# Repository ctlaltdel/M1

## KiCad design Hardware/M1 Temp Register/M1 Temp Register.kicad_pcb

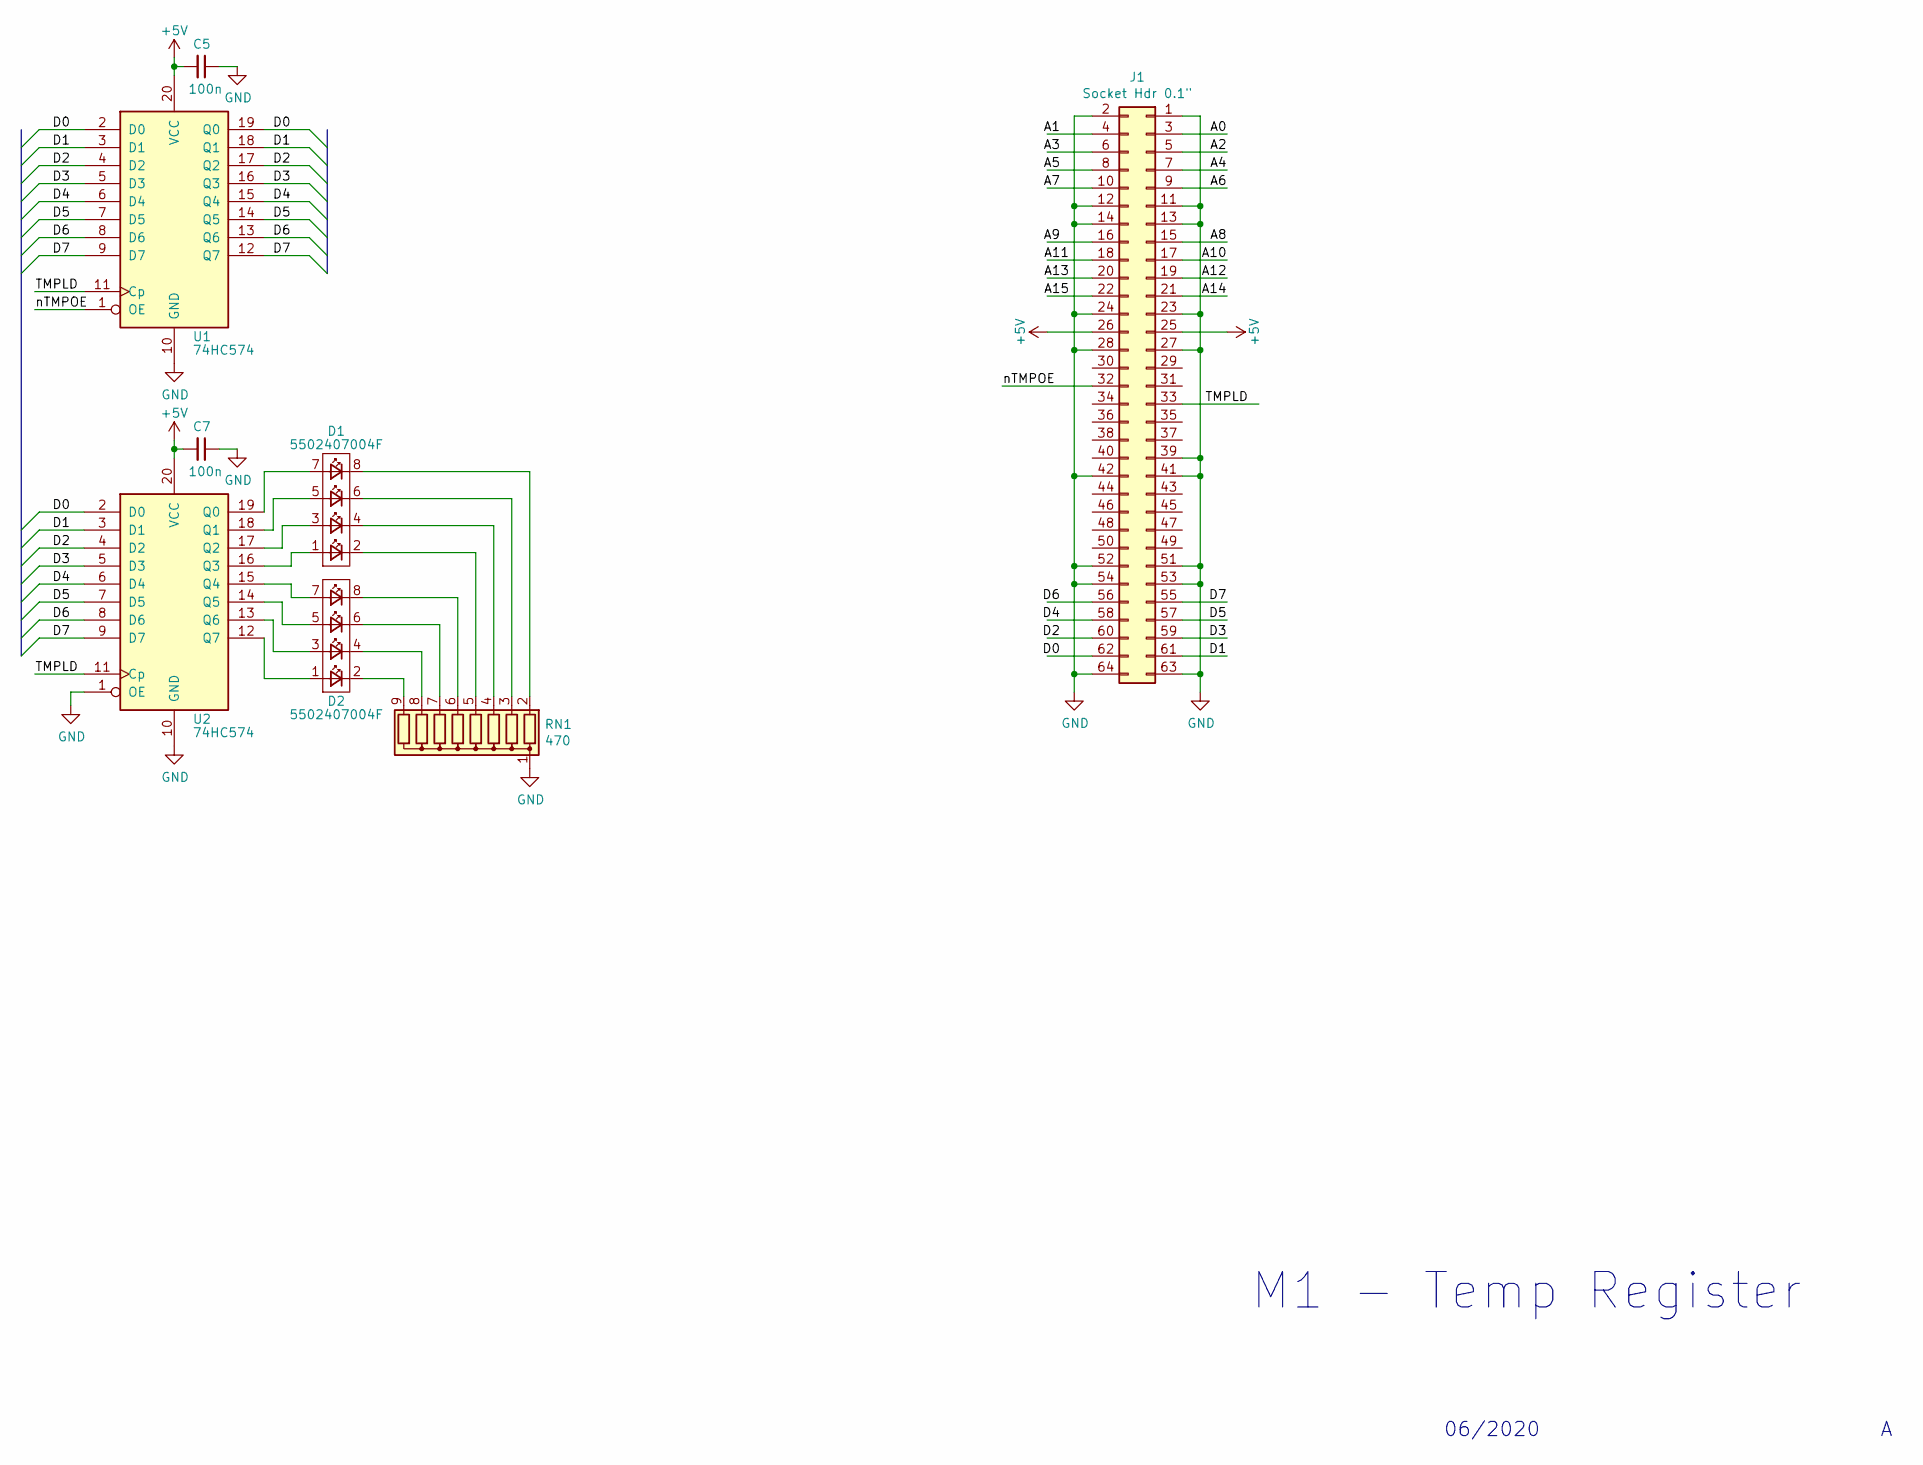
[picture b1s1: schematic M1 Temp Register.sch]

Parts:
C5, C7: 100n; C_Disc_D5.1mm_W3.2mm_P5.00mm
D1, D2: 5502407004F
J1: Socket Hdr 0.1\"; IDC-Header_2x32_P2.54mm_Horizontal
RN1: 470; R_Array_SIP9
U1, U2: 74HC574; DIP-20_W7.62mm_Socket

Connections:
+5V: C5.2, C7.2, J1.25, J1.26, U1.20 (VCC), U2.20 (VCC)
/A0: J1.3
/A1: J1.4
/A2: J1.5
/A3: J1.6
/A4: J1.7
/A5: J1.8
/A6: J1.9
/A7: J1.10
/A8: J1.15
/A9: J1.16
/A10: J1.17
/A11: J1.18
/A12: J1.19
/A13: J1.20
/A14: J1.21
/A15: J1.22
/D0: J1.62, U1.2 (D0), U1.19 (Q0), U2.2 (D0)
/D1: J1.61, U1.3 (D1), U1.18 (Q1), U2.3 (D1)
/D2: J1.60, U1.4 (D2), U1.17 (Q2), U2.4 (D2)
/D3: J1.59, U1.5 (D3), U1.16 (Q3), U2.5 (D3)
/D4: J1.58, U1.6 (D4), U1.15 (Q4), U2.6 (D4)
/D5: J1.57, U1.7 (D5), U1.14 (Q5), U2.7 (D5)
/D6: J1.56, U1.8 (D6), U1.13 (Q6), U2.8 (D6)
/D7: J1.55, U1.9 (D7), U1.12 (Q7), U2.9 (D7)
/TMPLD: J1.33, U1.11 (Cp), U2.11 (Cp)
/nTMPOE: J1.32, U1.1 (OE)
GND: C5.1, C7.1, J1.1, J1.2, J1.11, J1.12, J1.13, J1.14, J1.23, J1.24, J1.27, J1.28, J1.39, J1.41, J1.42, J1.51, J1.52, J1.53, J1.54, J1.63, J1.64, RN1.1 (common), U1.10 (GND), U2.1 (OE), U2.10 (GND)
unnamed: D1.1, U2.16 (Q3)
unnamed: D1.2, RN1.5 (R4)
unnamed: D1.3, U2.17 (Q2)
unnamed: D1.4, RN1.4 (R3)
unnamed: D1.5, U2.18 (Q1)
unnamed: D1.6, RN1.3 (R2)
unnamed: D1.7, U2.19 (Q0)
unnamed: D1.8, RN1.2 (R1)
unnamed: D2.1, U2.12 (Q7)
unnamed: D2.2, RN1.9 (R8)
unnamed: D2.3, U2.13 (Q6)
unnamed: D2.4, RN1.8 (R7)
unnamed: D2.5, U2.14 (Q5)
unnamed: D2.6, RN1.7 (R6)
unnamed: D2.7, U2.15 (Q4)
unnamed: D2.8, RN1.6 (R5)

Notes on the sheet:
M1 - Temp Register
06/2020

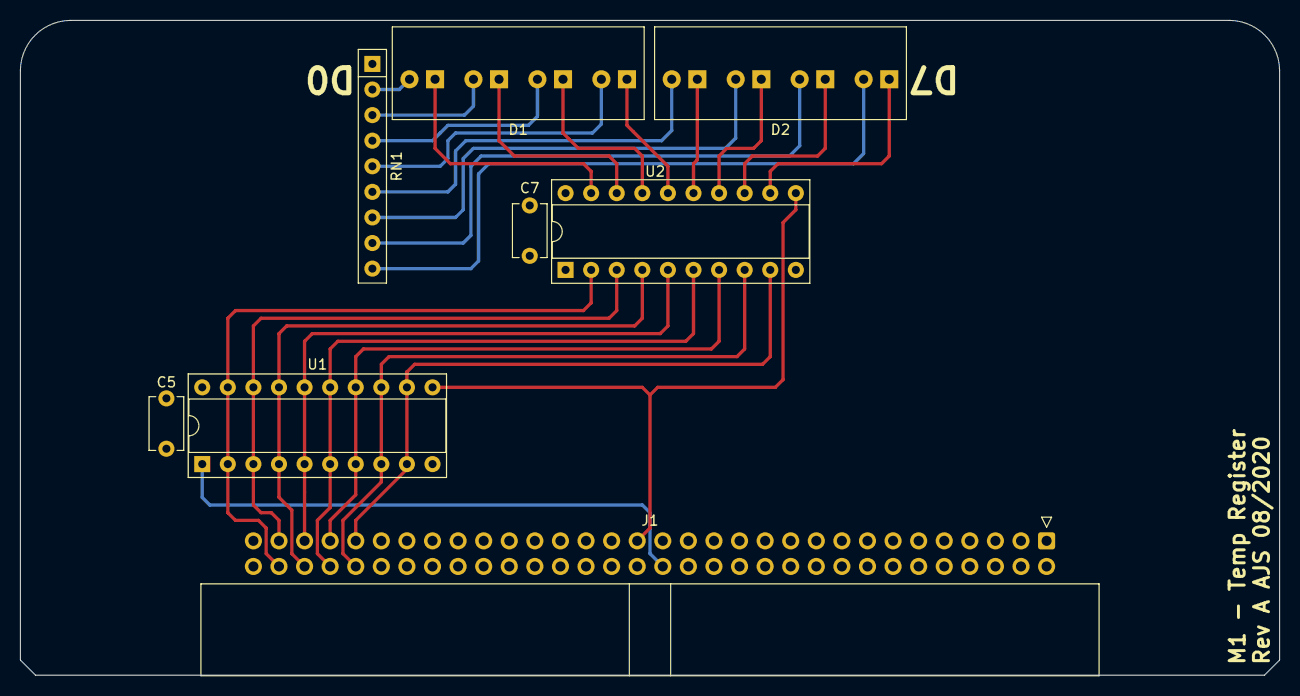
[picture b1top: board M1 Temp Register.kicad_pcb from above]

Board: 4 copper layers, 125.0 x 65.0 mm, 8 parts (0 on the bottom side), 28 nets.

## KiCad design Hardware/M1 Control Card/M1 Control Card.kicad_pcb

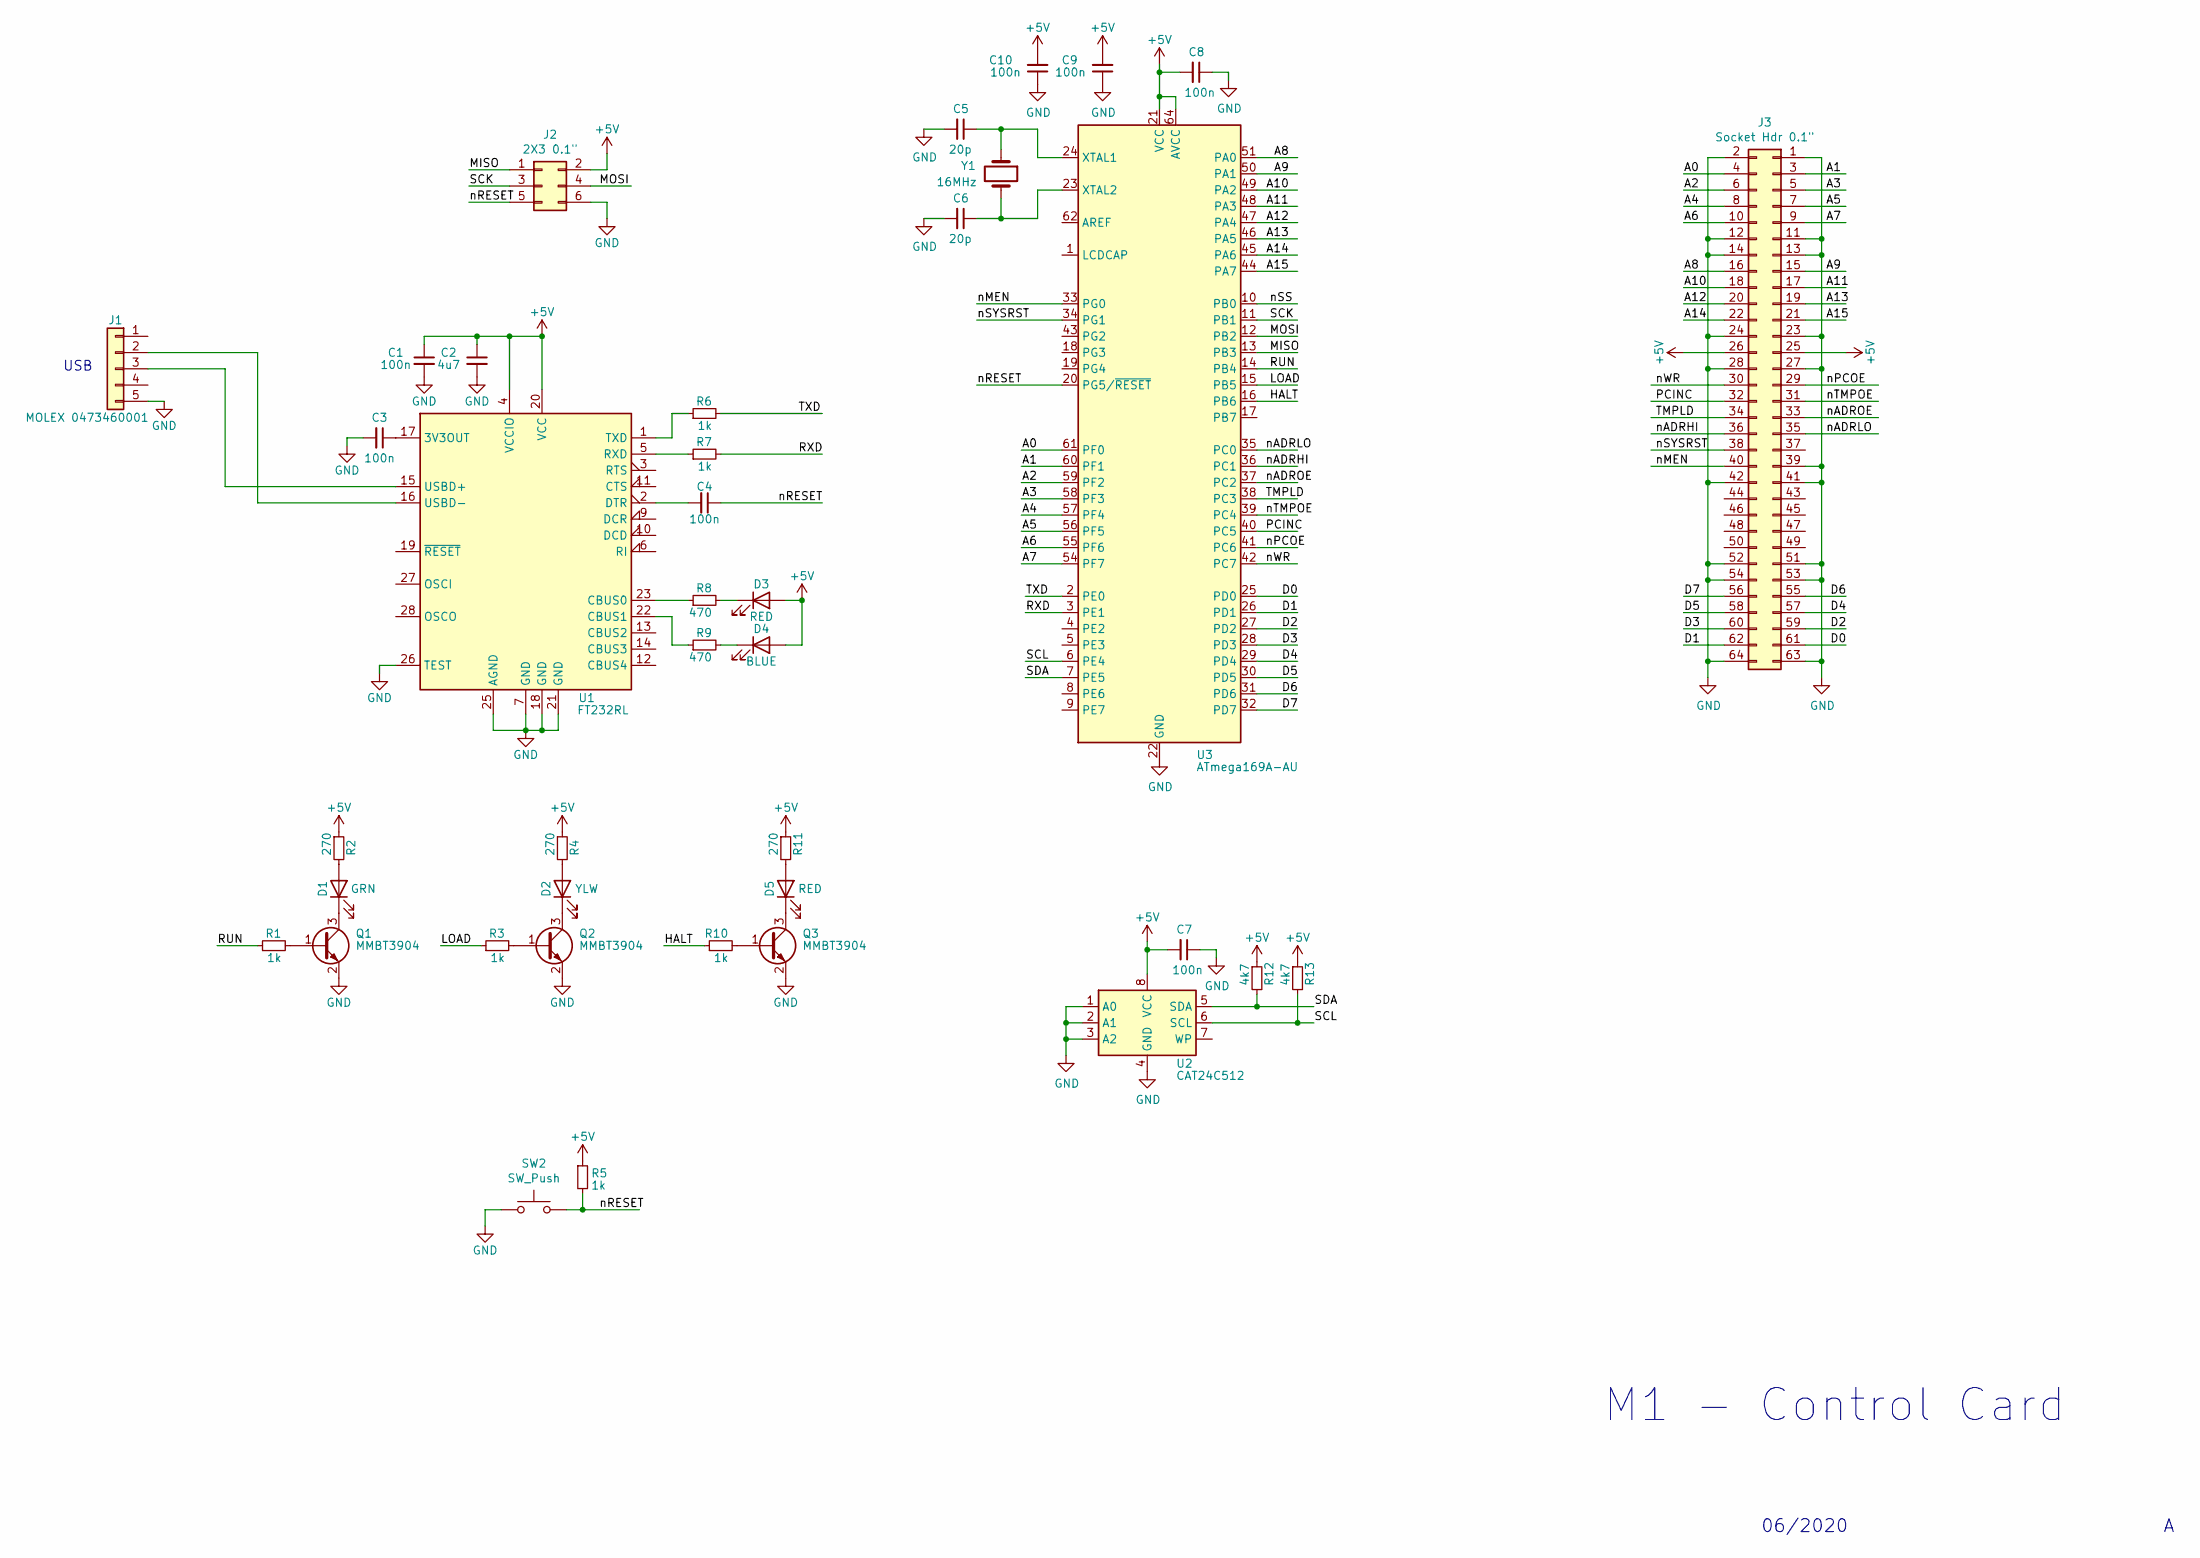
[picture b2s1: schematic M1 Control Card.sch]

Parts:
C1, C3, C4, C7, C8, C9, C10: 100n; C_0402_1005Metric
C2: 4u7; C_0603_1608Metric
C5, C6: 20p; C_0402_1005Metric
D1: GRN; LED_0603_1608Metric
D2: YLW; LED_0603_1608Metric
D3, D5: RED; LED_0603_1608Metric
D4: BLUE; LED_0603_1608Metric
J1: MOLEX 0473460001; USB_Micro-B_Molex_47346-0001
J2: 2X3 0.1\"; PinHeader_2x03_P2.54mm_Horizontal
J3: Socket Hdr 0.1\"; IDC-Header_2x32_P2.54mm_Horizontal
Q1, Q2, Q3: MMBT3904; SOT-23
R1, R3, R5, R6, R7, R10: 1k; R_0402_1005Metric
R2, R4, R11: 270; R_0402_1005Metric
R8, R9: 470; R_0402_1005Metric
R12, R13: 4k7; R_0402_1005Metric
SW2: SW_Push; SW_SPST_PTS645
U1: FT232RL; SSOP-28_5.3x10.2mm_P0.65mm
U2: CAT24C512; SOIC-8_3.9x4.9mm_P1.27mm
U3: ATmega169A-AU; TQFP-64_14x14mm_P0.8mm
Y1: 16MHz; Crystal_SMD_Abracon_ABM3-2Pin_5.0x3.2mm

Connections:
+5V: C1.1, C2.1, C7.2, C8.2, C9.2, C10.2, D3.2 (A), D4.2 (A), J2.2, J3.25, J3.26, R2.1, R4.1, R5.1, R11.1, R12.1, R13.1, U1.4 (VCCIO), U1.20 (VCC), U2.8 (VCC), U3.21 (VCC), U3.52 (VCC), U3.64 (AVCC)
/A0: J3.4, U3.61 (PF0)
/A1: J3.3, U3.60 (PF1)
/A2: J3.6, U3.59 (PF2)
/A3: J3.5, U3.58 (PF3)
/A4: J3.8, U3.57 (PF4)
/A5: J3.7, U3.56 (PF5)
/A6: J3.10, U3.55 (PF6)
/A7: J3.9, U3.54 (PF7)
/A8: J3.16, U3.51 (PA0)
/A9: J3.15, U3.50 (PA1)
/A10: J3.18, U3.49 (PA2)
/A11: J3.17, U3.48 (PA3)
/A12: J3.20, U3.47 (PA4)
/A13: J3.19, U3.46 (PA5)
/A14: J3.22, U3.45 (PA6)
/A15: J3.21, U3.44 (PA7)
/ADRHI: J3.36, U3.36 (PC1)
/D0: J3.61, U3.25 (PD0)
/D1: J3.62, U3.26 (PD1)
/D2: J3.59, U3.27 (PD2)
/D3: J3.60, U3.28 (PD3)
/D4: J3.57, U3.29 (PD4)
/D5: J3.58, U3.30 (PD5)
/D6: J3.55, U3.31 (PD6)
/D7: J3.56, U3.32 (PD7)
/HALT: R10.1, U3.16 (PB6)
/LOAD: R3.1, U3.15 (PB5)
/MISO: J2.1, U3.13 (PB3)
/MOSI: J2.4, U3.12 (PB2)
/PCINC: J3.32, U3.40 (PC5)
/RUN: R1.1, U3.14 (PB4)
/RXD: R7.2, U3.3 (PE1)
/SCK: J2.3, U3.11 (PB1)
/SCL: R13.2, U2.6 (SCL), U3.6 (PE4)
/SDA: R12.2, U2.5 (SDA), U3.7 (PE5)
/TMPLD: J3.34, U3.38 (PC3)
/TXD: R6.2, U3.2 (PE0)
/nADRLO: J3.35, U3.35 (PC0)
/nADROE: J3.33, U3.37 (PC2)
/nMEN: J3.40, U3.33 (PG0)
/nPCOE: J3.29, U3.41 (PC6)
/nRESET: C4.1, J2.5, R5.2, SW2.2, U3.20 (PG5/~RESET)
/nSS: U3.10 (PB0)
/nSYSRST: J3.38, U3.34 (PG1)
/nTMPOE: J3.31, U3.39 (PC4)
/nWR: J3.30, U3.42 (PC7)
GND: C1.2, C2.2, C3.2, C5.2, C6.2, C7.1, C8.1, C9.1, C10.1, J1.5, J2.6, J3.1, J3.2, J3.11, J3.12, J3.13, J3.14, J3.23, J3.24, J3.27, J3.28, J3.39, J3.41, J3.42, J3.51, J3.52, J3.53, J3.54, J3.63, J3.64, Q1.2 (E), Q2.2 (E), Q3.2 (E), SW2.1, U1.7 (GND), U1.18 (GND), U1.21 (GND), U1.25 (AGND), U1.26 (TEST), U2.1 (A0), U2.2 (A1), U2.3 (A2), U2.4 (GND), U3.22 (GND), U3.53 (GND), U3.63 (GND)
unnamed: C3.1, U1.17 (3V3OUT)
unnamed: C4.2, U1.2 (DTR)
unnamed: C5.1, U3.24 (XTAL1), Y1.1
unnamed: C6.1, U3.23 (XTAL2), Y1.2
unnamed: D1.1 (K), Q1.3 (C)
unnamed: D1.2 (A), R2.2
unnamed: D2.1 (K), Q2.3 (C)
unnamed: D2.2 (A), R4.2
unnamed: D3.1 (K), R8.2
unnamed: D4.1 (K), R9.2
unnamed: D5.1 (K), Q3.3 (C)
unnamed: D5.2 (A), R11.2
unnamed: J1.2, U1.16 (USBD-)
unnamed: J1.3, U1.15 (USBD+)
unnamed: Q1.1 (B), R1.2
unnamed: Q2.1 (B), R3.2
unnamed: Q3.1 (B), R10.2
unnamed: R6.1, U1.1 (TXD)
unnamed: R7.1, U1.5 (RXD)
unnamed: R8.1, U1.23 (CBUS0)
unnamed: R9.1, U1.22 (CBUS1)

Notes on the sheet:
USB
M1 - Control Card
06/2020

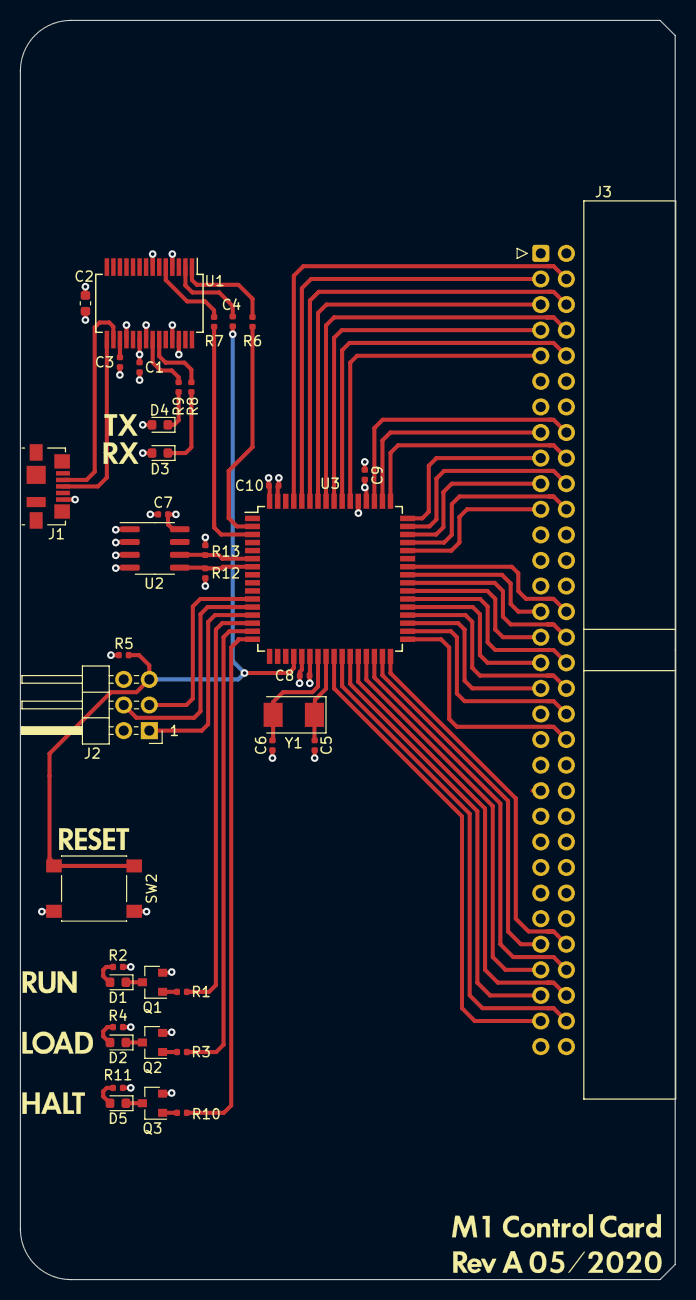
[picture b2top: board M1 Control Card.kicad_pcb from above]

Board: 4 copper layers, 65.0 x 125.0 mm, 39 parts (0 on the bottom side), 68 nets.

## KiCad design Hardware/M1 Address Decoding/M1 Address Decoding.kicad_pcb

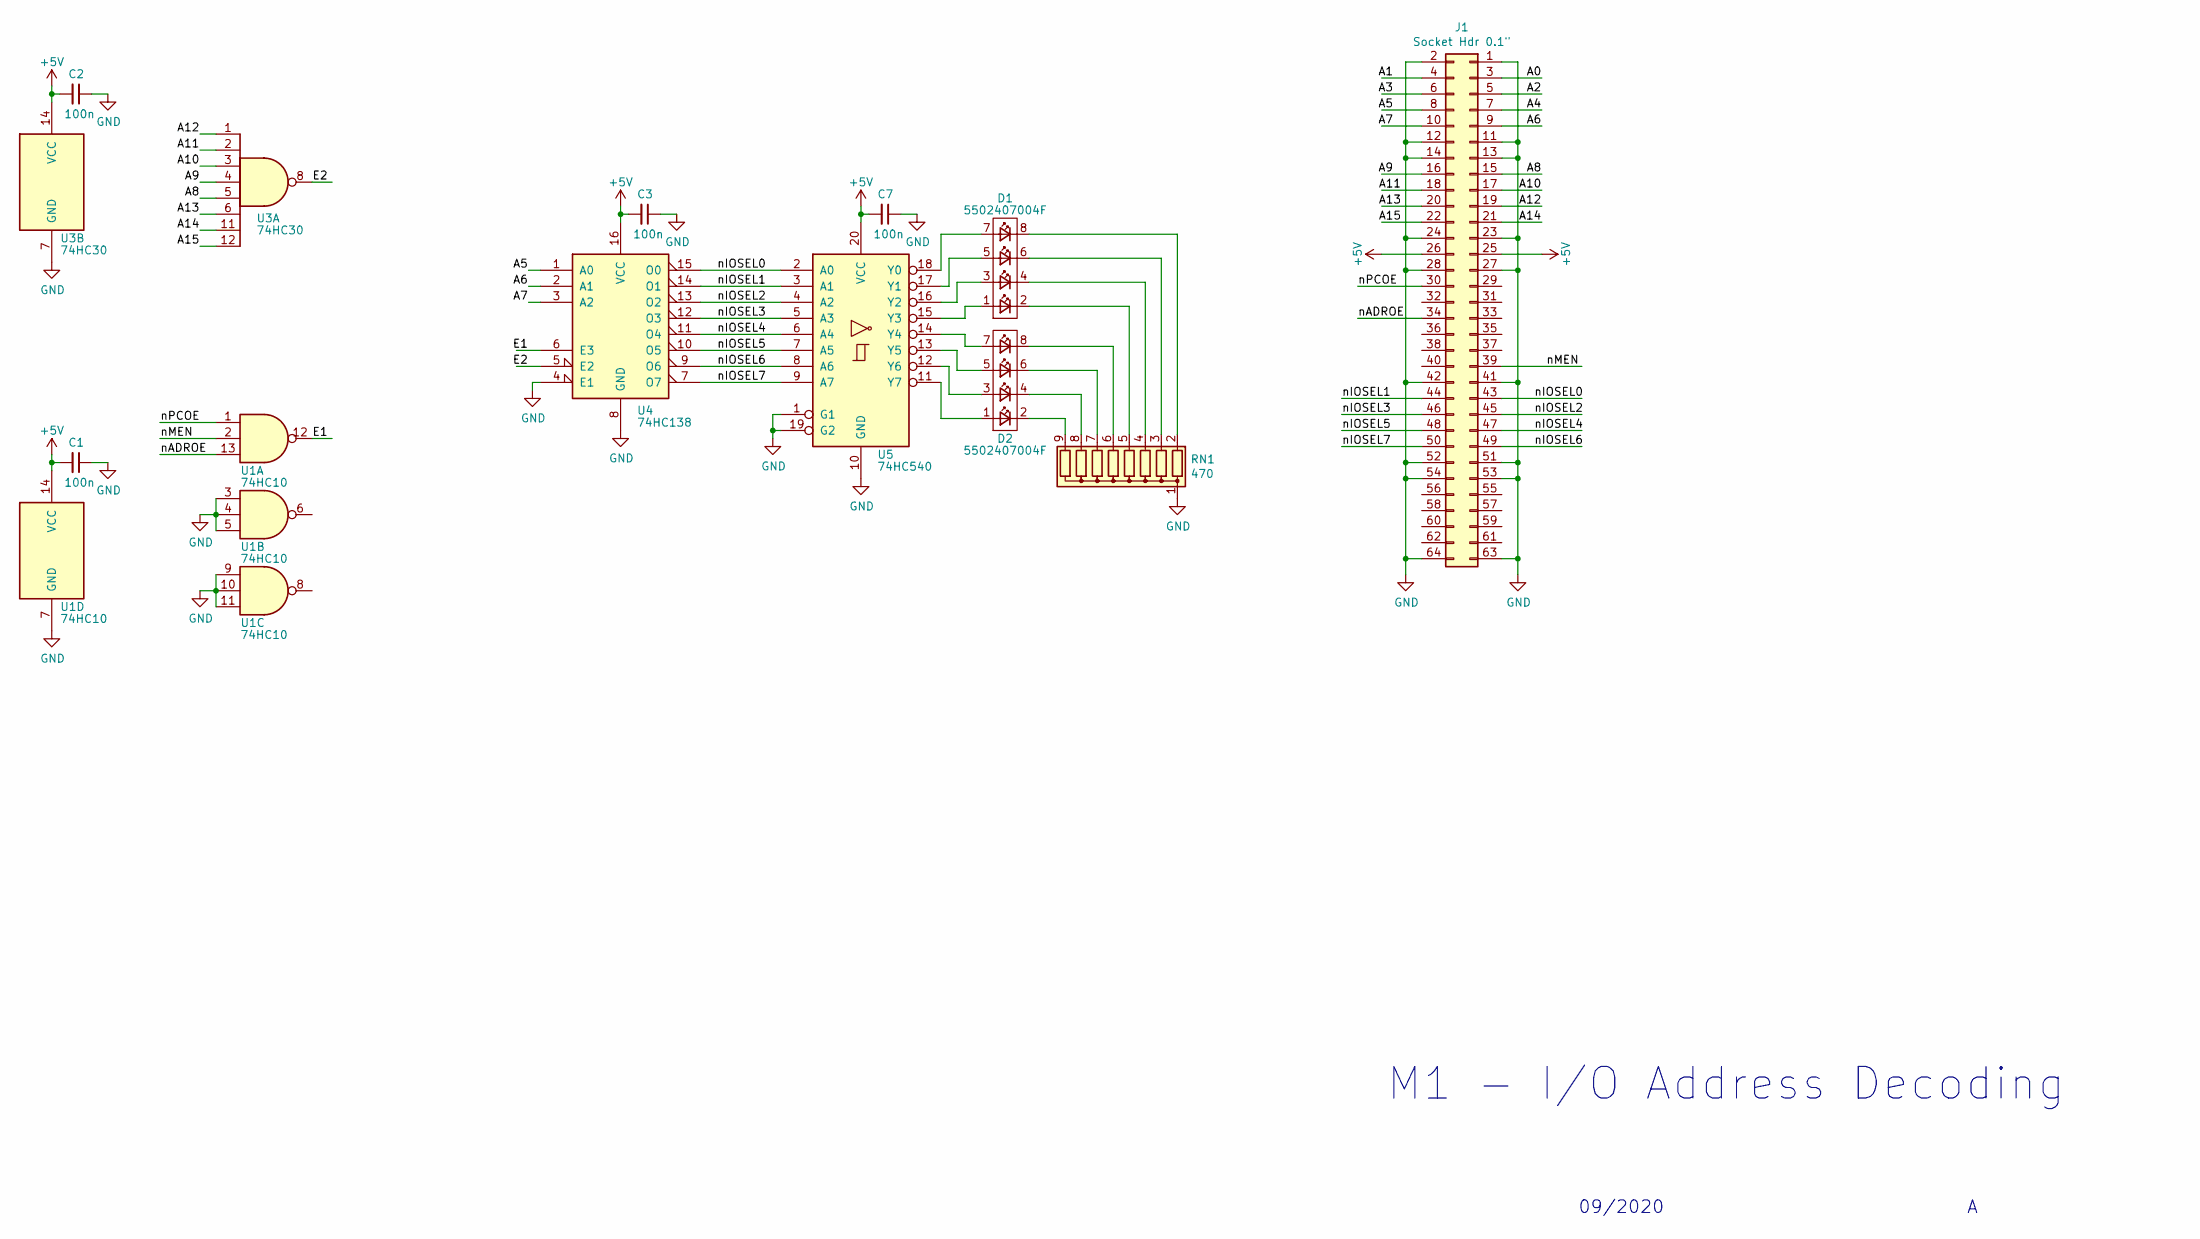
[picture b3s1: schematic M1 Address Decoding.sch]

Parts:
C1, C2, C3, C7: 100n; C_Disc_D5.1mm_W3.2mm_P5.00mm
D1, D2: 5502407004F
J1: Socket Hdr 0.1\"; IDC-Header_2x32_P2.54mm_Horizontal
RN1: 470; R_Array_SIP9
U1: 74HC10; DIP-14_W7.62mm_Socket
U3: 74HC30; DIP-14_W7.62mm_Socket
U4: 74HC138; DIP-16_W7.62mm_Socket
U5: 74HC540; DIP-20_W7.62mm_Socket

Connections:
+5V: C1.2, C2.2, C3.2, C7.2, J1.25, J1.26, U1.14 (VCC), U3.14 (VCC), U4.16 (VCC), U5.20 (VCC)
/A0: J1.3
/A1: J1.4
/A2: J1.5
/A3: J1.6
/A4: J1.7
/A5: J1.8, U4.1 (A0)
/A6: J1.9, U4.2 (A1)
/A7: J1.10, U4.3 (A2)
/A8: J1.15, U3.5
/A9: J1.16, U3.4
/A10: J1.17, U3.3
/A11: J1.18, U3.2
/A12: J1.19, U3.1
/A13: J1.20, U3.6
/A14: J1.21, U3.11
/A15: J1.22, U3.12
/E1: U1.12, U4.6 (E3)
/E2: U3.8, U4.5 (E2)
/nADROE: J1.34, U1.13
/nIOSEL0: J1.43, U4.15 (O0), U5.2 (A0)
/nIOSEL1: J1.44, U4.14 (O1), U5.3 (A1)
/nIOSEL2: J1.45, U4.13 (O2), U5.4 (A2)
/nIOSEL3: J1.46, U4.12 (O3), U5.5 (A3)
/nIOSEL4: J1.47, U4.11 (O4), U5.6 (A4)
/nIOSEL5: J1.48, U4.10 (O5), U5.7 (A5)
/nIOSEL6: J1.49, U4.9 (O6), U5.8 (A6)
/nIOSEL7: J1.50, U4.7 (O7), U5.9 (A7)
/nMEN: J1.39, U1.2
/nPCOE: J1.30, U1.1
GND: C1.1, C2.1, C3.1, C7.1, J1.1, J1.2, J1.11, J1.12, J1.13, J1.14, J1.23, J1.24, J1.27, J1.28, J1.41, J1.42, J1.51, J1.52, J1.53, J1.54, J1.63, J1.64, RN1.1 (common), U1.3, U1.4, U1.5, U1.7 (GND), U1.9, U1.10, U1.11, U3.7 (GND), U4.4 (E1), U4.8 (GND), U5.1 (G1), U5.10 (GND), U5.19 (G2)
unnamed: D1.1, U5.15 (Y3)
unnamed: D1.2, RN1.5 (R4)
unnamed: D1.3, U5.16 (Y2)
unnamed: D1.4, RN1.4 (R3)
unnamed: D1.5, U5.17 (Y1)
unnamed: D1.6, RN1.3 (R2)
unnamed: D1.7, U5.18 (Y0)
unnamed: D1.8, RN1.2 (R1)
unnamed: D2.1, U5.11 (Y7)
unnamed: D2.2, RN1.9 (R8)
unnamed: D2.3, U5.12 (Y6)
unnamed: D2.4, RN1.8 (R7)
unnamed: D2.5, U5.13 (Y5)
unnamed: D2.6, RN1.7 (R6)
unnamed: D2.7, U5.14 (Y4)
unnamed: D2.8, RN1.6 (R5)

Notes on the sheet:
M1 - I/O Address Decoding
09/2020

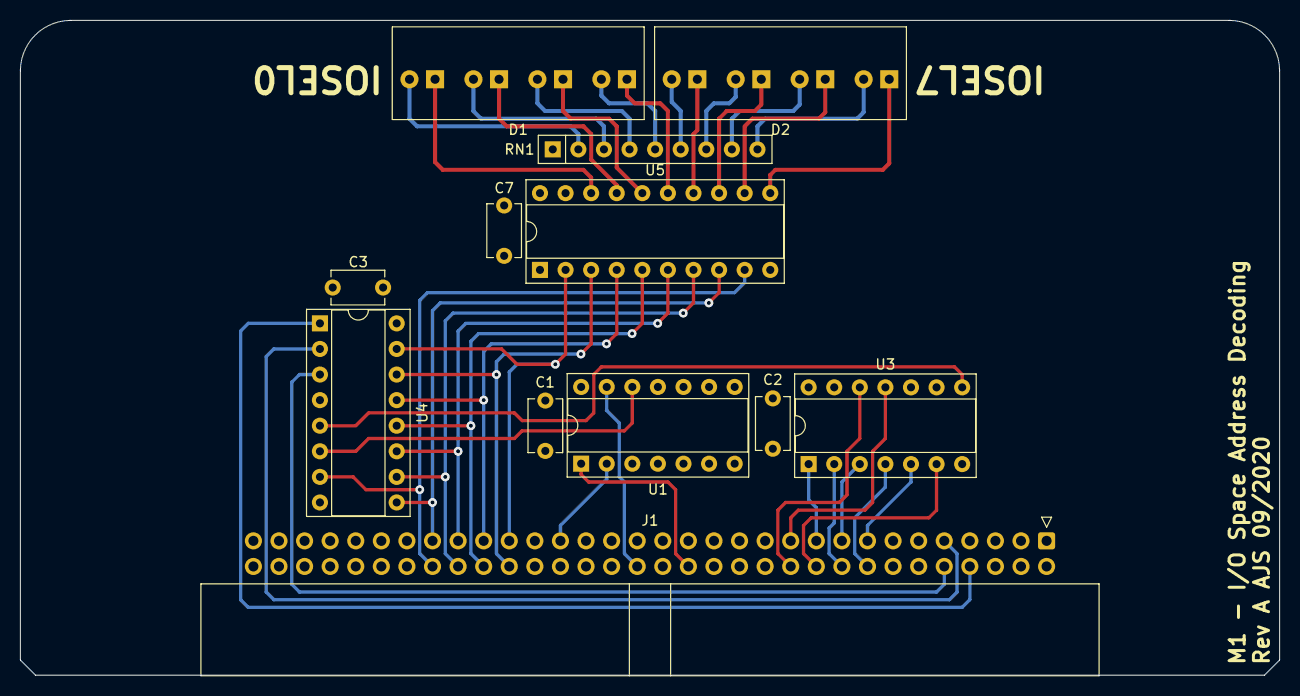
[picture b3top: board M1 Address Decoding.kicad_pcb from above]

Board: 4 copper layers, 125.0 x 65.0 mm, 12 parts (0 on the bottom side), 42 nets.

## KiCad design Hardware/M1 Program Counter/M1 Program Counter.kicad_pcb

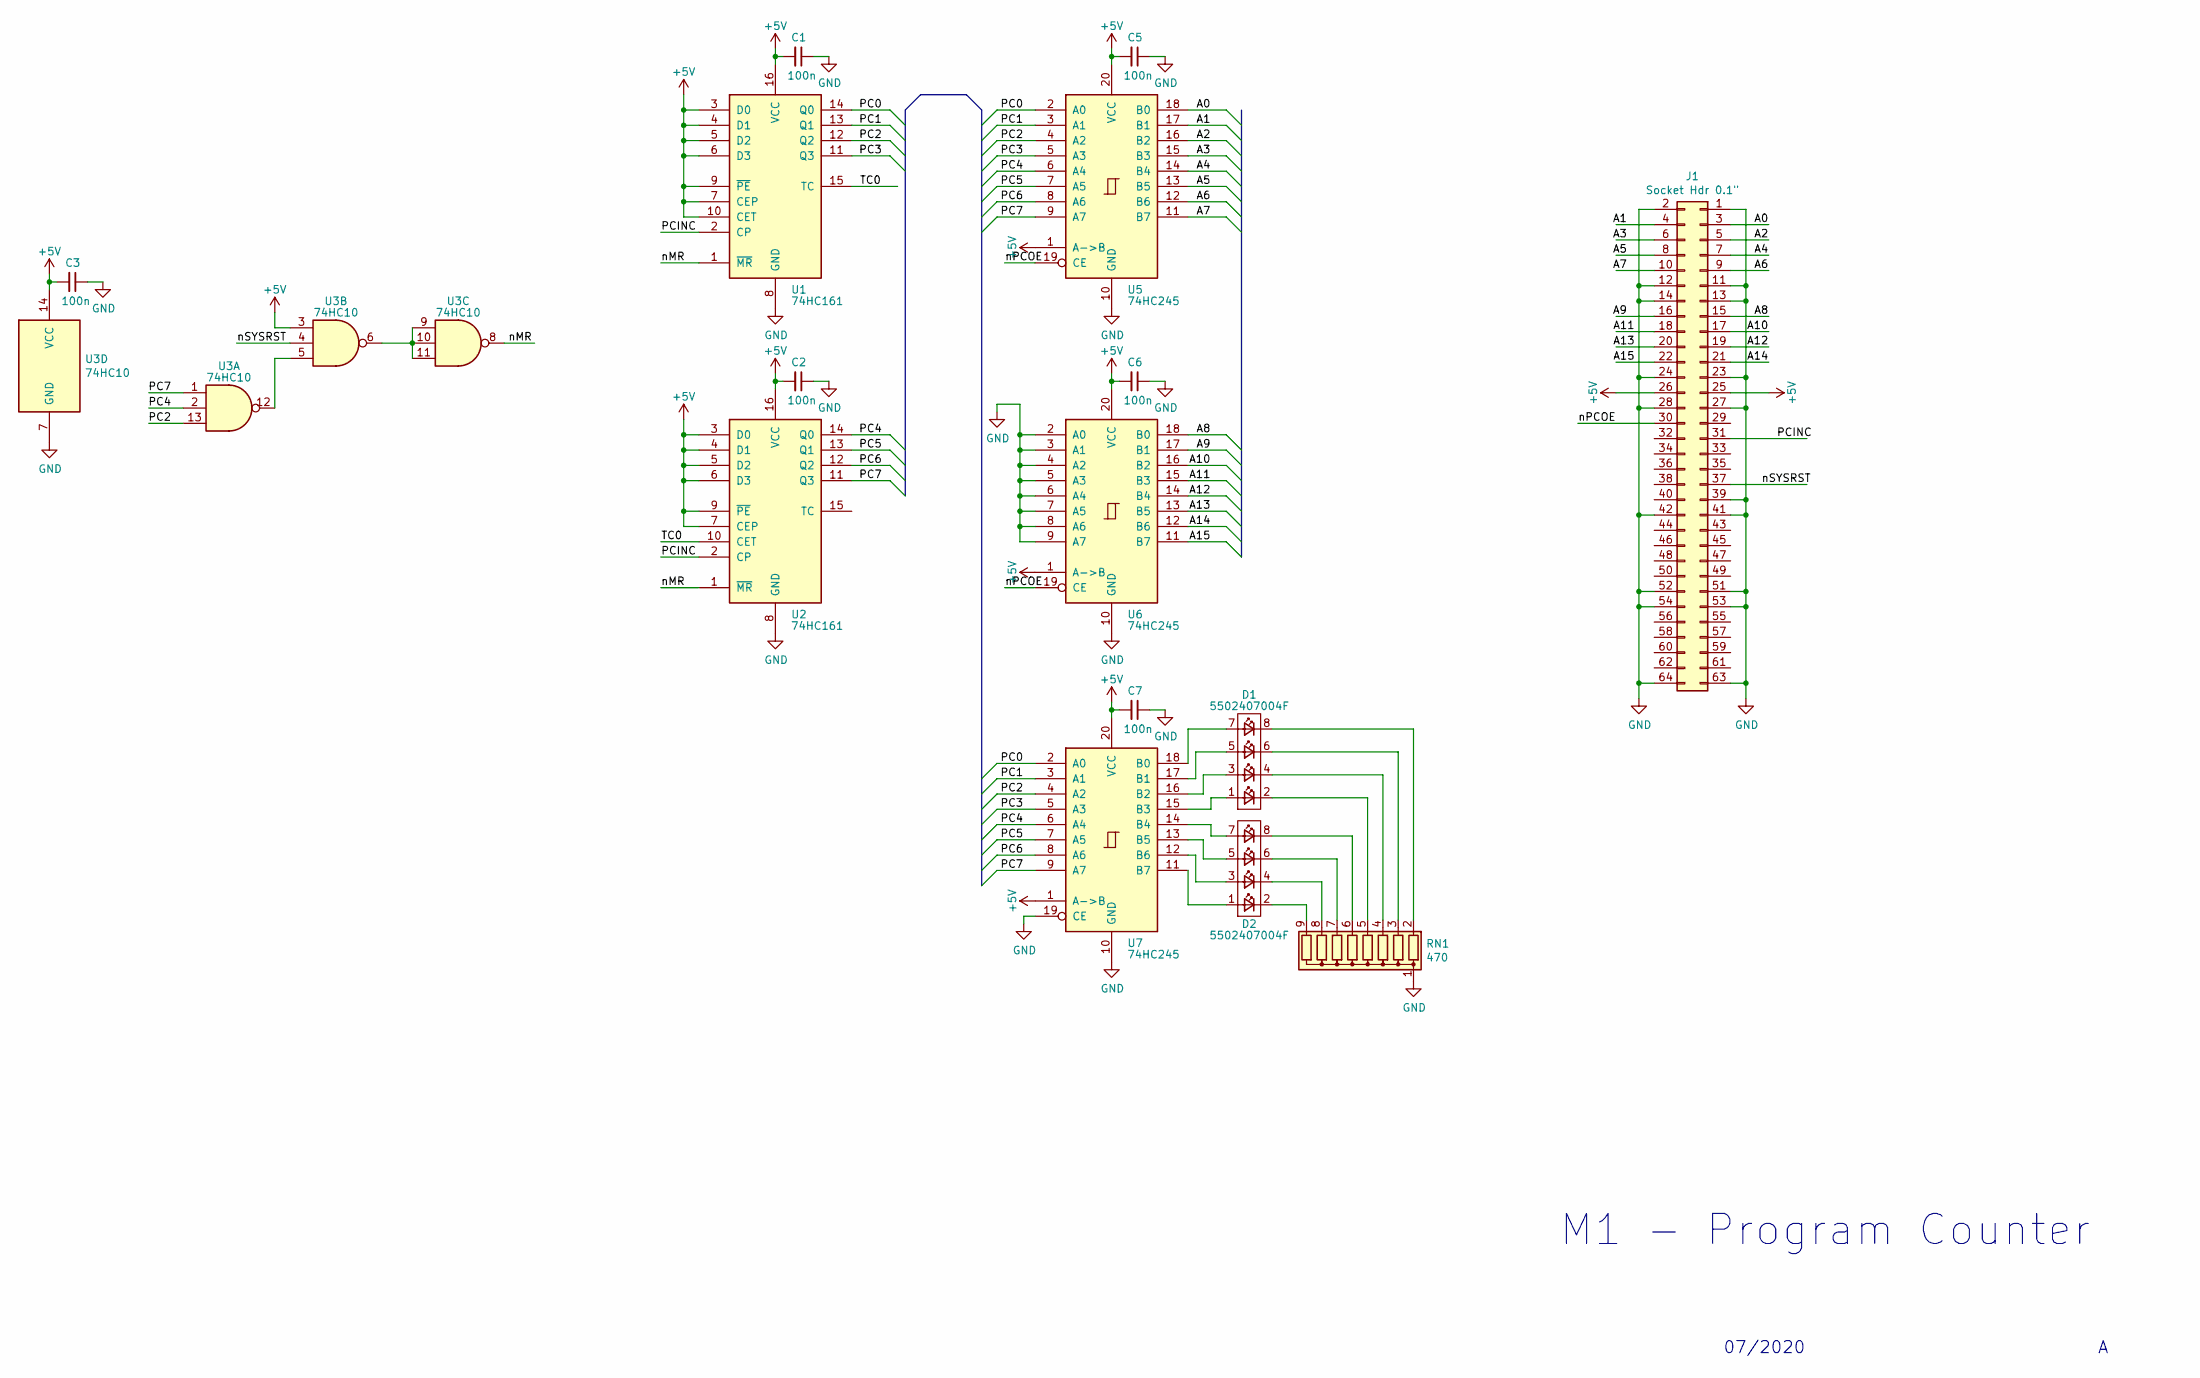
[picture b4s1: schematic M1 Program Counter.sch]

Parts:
C1, C2, C3, C5, C6, C7: 100n; C_Disc_D5.1mm_W3.2mm_P5.00mm
D1, D2: 5502407004F
J1: Socket Hdr 0.1\"; IDC-Header_2x32_P2.54mm_Horizontal
RN1: 470; R_Array_SIP9
U1, U2: 74HC161; DIP-16_W7.62mm_Socket
U3: 74HC10; DIP-14_W7.62mm_Socket
U5, U6, U7: 74HC245; DIP-20_W7.62mm_Socket

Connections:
+5V: C1.2, C2.2, C3.2, C5.2, C6.2, C7.2, J1.25, J1.26, U1.3 (D0), U1.4 (D1), U1.5 (D2), U1.6 (D3), U1.7 (CEP), U1.9 (~PE), U1.10 (CET), U1.16 (VCC), U2.3 (D0), U2.4 (D1), U2.5 (D2), U2.6 (D3), U2.7 (CEP), U2.9 (~PE), U2.16 (VCC), U3.3, U3.14 (VCC), U5.1 (A->B), U5.20 (VCC), U6.1 (A->B), U6.20 (VCC), U7.1 (A->B), U7.20 (VCC)
/A0: J1.3, U5.18 (B0)
/A1: J1.4, U5.17 (B1)
/A2: J1.5, U5.16 (B2)
/A3: J1.6, U5.15 (B3)
/A4: J1.7, U5.14 (B4)
/A5: J1.8, U5.13 (B5)
/A6: J1.9, U5.12 (B6)
/A7: J1.10, U5.11 (B7)
/A8: J1.15, U6.18 (B0)
/A9: J1.16, U6.17 (B1)
/A10: J1.17, U6.16 (B2)
/A11: J1.18, U6.15 (B3)
/A12: J1.19, U6.14 (B4)
/A13: J1.20, U6.13 (B5)
/A14: J1.21, U6.12 (B6)
/A15: J1.22, U6.11 (B7)
/PC0: U1.14 (Q0), U5.2 (A0), U7.2 (A0)
/PC1: U1.13 (Q1), U5.3 (A1), U7.3 (A1)
/PC2: U1.12 (Q2), U3.13, U5.4 (A2), U7.4 (A2)
/PC3: U1.11 (Q3), U5.5 (A3), U7.5 (A3)
/PC4: U2.14 (Q0), U3.2, U5.6 (A4), U7.6 (A4)
/PC5: U2.13 (Q1), U5.7 (A5), U7.7 (A5)
/PC6: U2.12 (Q2), U5.8 (A6), U7.8 (A6)
/PC7: U2.11 (Q3), U3.1, U5.9 (A7), U7.9 (A7)
/PCINC: J1.31, U1.2 (CP), U2.2 (CP)
/TC0: U1.15 (TC), U2.10 (CET)
/nMR: U1.1 (~MR), U2.1 (~MR), U3.8
/nPCOE: J1.30, U5.19 (CE), U6.19 (CE)
/nSYSRST: J1.37, U3.4
GND: C1.1, C2.1, C3.1, C5.1, C6.1, C7.1, J1.1, J1.2, J1.11, J1.12, J1.13, J1.14, J1.23, J1.24, J1.27, J1.28, J1.39, J1.41, J1.42, J1.51, J1.52, J1.53, J1.54, J1.63, J1.64, RN1.1 (common), U1.8 (GND), U2.8 (GND), U3.7 (GND), U5.10 (GND), U6.2 (A0), U6.3 (A1), U6.4 (A2), U6.5 (A3), U6.6 (A4), U6.7 (A5), U6.8 (A6), U6.9 (A7), U6.10 (GND), U7.10 (GND), U7.19 (CE)
unnamed: D1.1, U7.15 (B3)
unnamed: D1.2, RN1.5 (R4)
unnamed: D1.3, U7.16 (B2)
unnamed: D1.4, RN1.4 (R3)
unnamed: D1.5, U7.17 (B1)
unnamed: D1.6, RN1.3 (R2)
unnamed: D1.7, U7.18 (B0)
unnamed: D1.8, RN1.2 (R1)
unnamed: D2.1, U7.11 (B7)
unnamed: D2.2, RN1.9 (R8)
unnamed: D2.3, U7.12 (B6)
unnamed: D2.4, RN1.8 (R7)
unnamed: D2.5, U7.13 (B5)
unnamed: D2.6, RN1.7 (R6)
unnamed: D2.7, U7.14 (B4)
unnamed: D2.8, RN1.6 (R5)
unnamed: U3.6, U3.9, U3.10, U3.11
unnamed: U3.5, U3.12

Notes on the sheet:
M1 - Program Counter
07/2020

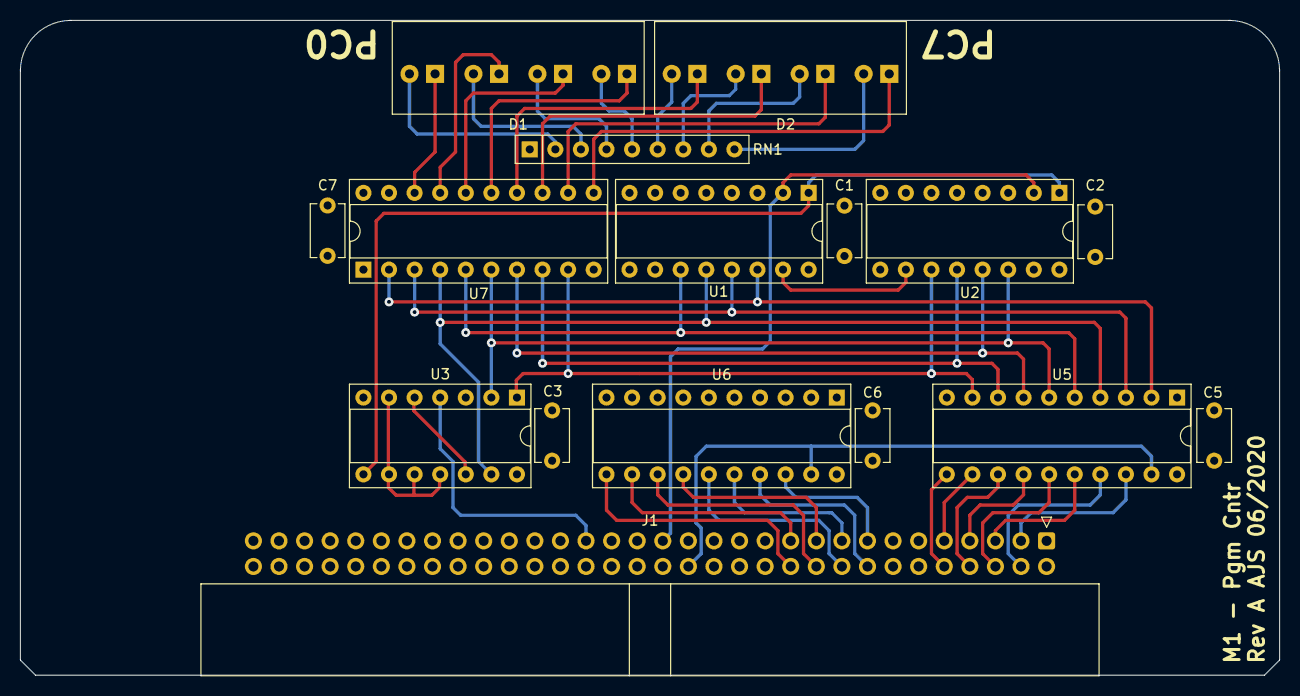
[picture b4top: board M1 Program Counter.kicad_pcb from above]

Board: 4 copper layers, 125.0 x 65.0 mm, 16 parts (0 on the bottom side), 49 nets.
